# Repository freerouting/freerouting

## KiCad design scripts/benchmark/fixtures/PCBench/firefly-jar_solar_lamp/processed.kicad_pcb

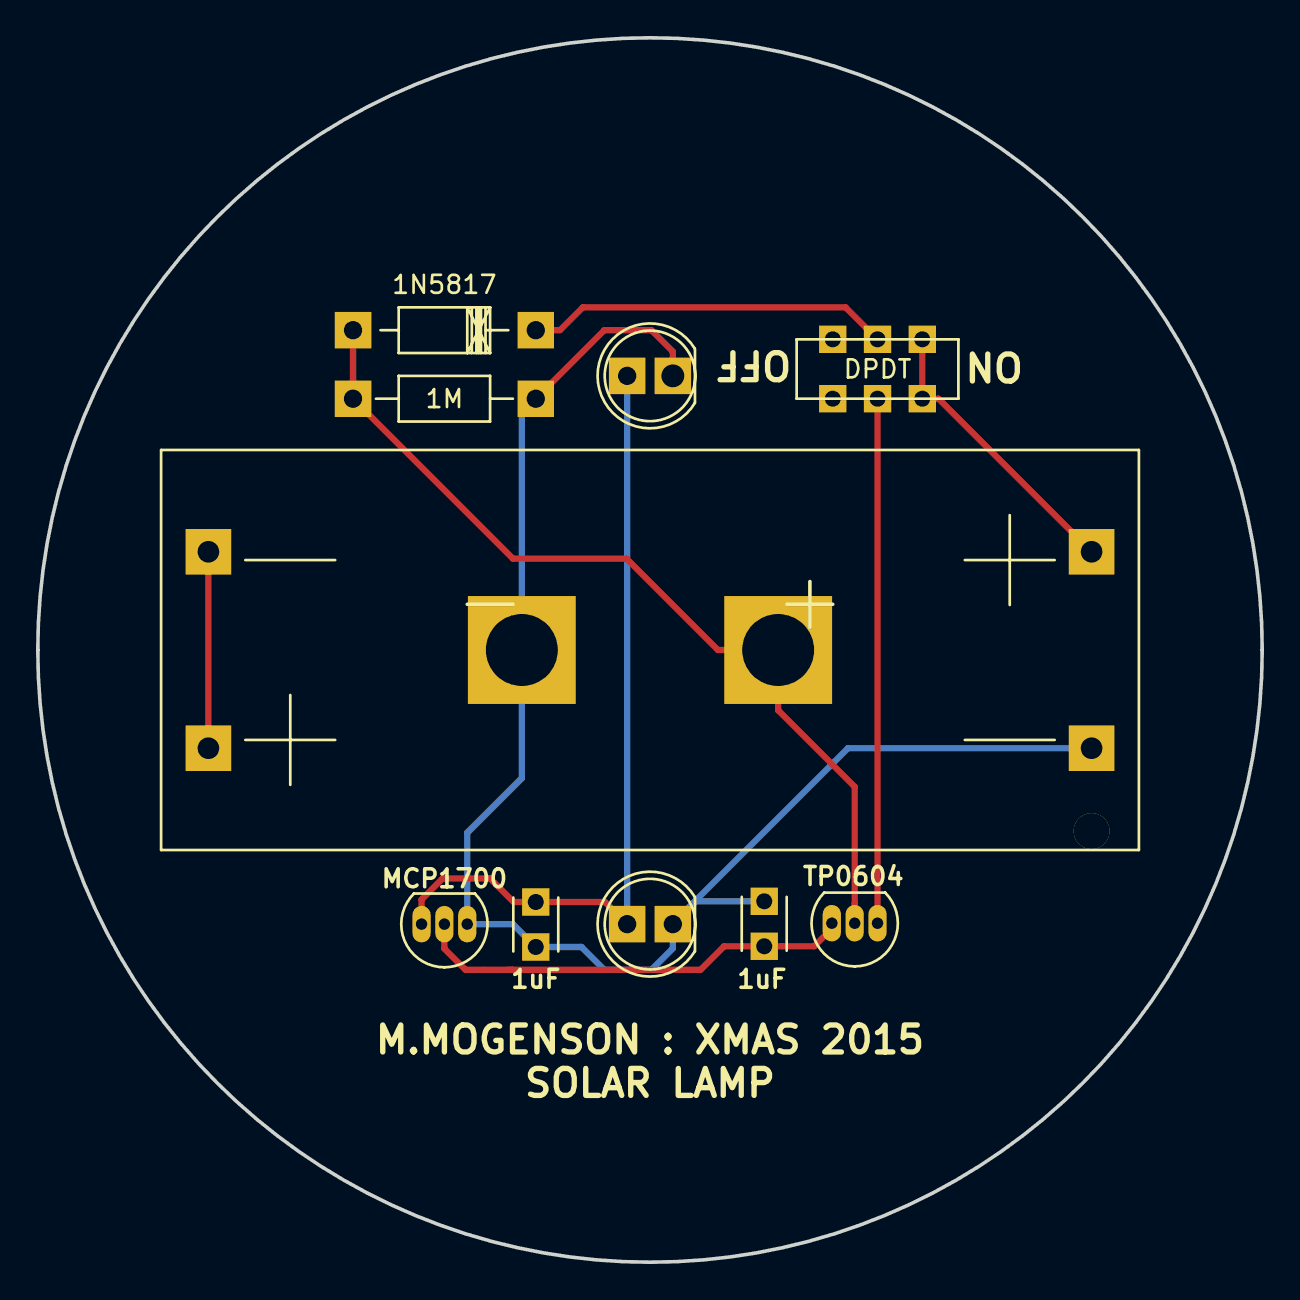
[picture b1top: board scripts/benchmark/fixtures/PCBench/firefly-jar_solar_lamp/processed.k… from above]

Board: 2 copper layers, 68.1 x 68.1 mm, 11 parts (1 on the bottom side), 8 nets.

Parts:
B1: 2x_AAA_battery; Keystone_1077_2x_AAA_battery_holder
BT1: Solar Cell; Adafruit_round_solar_panel
C1, C2: 1uF; C_Disc_D3_P2.5
D1: 1N5817; Diode_DO-41_SOD81_Horizontal_RM10
D2, D3: LED; LED-5MM
Q1: TP0604; TO-92_Inline_Narrow_Oval
R1: 1M; Resistor_Horizontal_RM10mm
SW1: DPDT; DPDT_JS202011CQN_switch
U1: MCP1700; TO-92_Inline_Narrow_Oval

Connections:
GND: B1.2, BT1.2, C1.2, C2.2, D2.1, D3.1, R1.2, U1.1
unnamed: B1.1, B1.4
unnamed: B1.3, SW1.1, SW1.4
unnamed: BT1.1, D1.2, Q1.2, R1.1
unnamed: C1.1, Q1.3, U1.2
unnamed: C2.1, D2.2, D3.2, U1.3
unnamed: D1.1, SW1.2
unnamed: Q1.1, SW1.5

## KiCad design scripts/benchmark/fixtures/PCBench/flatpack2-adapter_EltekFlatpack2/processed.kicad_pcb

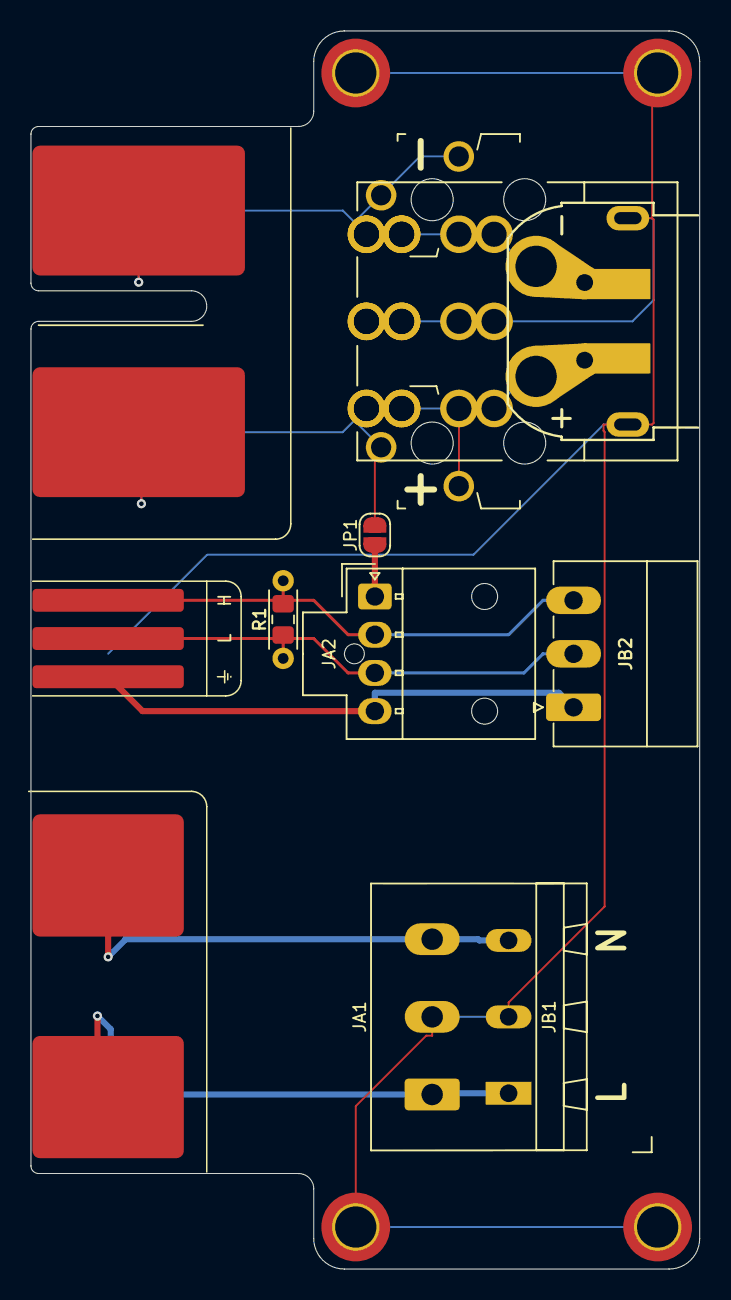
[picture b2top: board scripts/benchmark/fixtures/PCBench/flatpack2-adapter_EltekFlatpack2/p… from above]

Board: 2 copper layers, 43.8 x 81.0 mm, 17 parts (0 on the bottom side), 9 nets.

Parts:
H1, H2, H3, H4: M3; MountingHole_2.7mm_M2.5_ISO7380_Pad_TopBottom
JA1: AC_IN; 1605540000
JA2: CTRL; Molex_Nano-Fit_105309-xx04_1x04_P2.50mm_Combi_3D-V
JA3: DC OUT; TE_2204529-1
JB1: AC_IN; TerminalBlock_WAGO_236-103_1x03_P5.00mm_PadsOnly
JB2: CANBUS; PhoenixContact_MC_1,5_3-G-3.5_1x03_P3.50mm_Horizontal
JB3: DC OUT; TE_2204535-1
JC3: DC OUT; Amass_XT60PW-M_Kombifootprint
JP1: CTRL_VBUS+; SolderJumper-2_P1.3mm_Open_RoundedPad1.0x1.5mm
PC1: Flatpack2; CON_Edge_Flatpack2_AllContacts
R1: 120R; R_0805_2012Metric_Pad1.15x1.40mm_HandSolder
R2: 120R; R_Axial_DIN0204_L3.6mm_D1.6mm_P5.08mm_Horizontal
T1, T2: Keystone 4912; Connector_Keystone_4912_Overlaid

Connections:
/CAN+: JA2.2, JB2.3, PC1.CAN-H, R1.2, R2.2
/CAN-: JA2.3, JB2.2, PC1.CAN-L, R1.1, R2.1
/VBUS+: JA3.1, JB3.1, JB3.4, JC3.2, JP1.1, PC1.DC-POS, T1.1
/VBUS-: JA3.3, JB3.3, JB3.6, JC3.1, PC1.DC-NEG, T2.1
/VCCD: JA2.1, JP1.2
Earth: H1.1, H2.1, H3.1, H4.1, JA1.2, JA3.2, JB1.2, JB3.2, JB3.5, JC3.MP, PC1.AC-E
GNDD: JA2.4, JB2.1, PC1.GNDD
LINE: JA1.1, JB1.1, PC1.AC-L
NEUT: JA1.3, JB1.3, PC1.AC-N

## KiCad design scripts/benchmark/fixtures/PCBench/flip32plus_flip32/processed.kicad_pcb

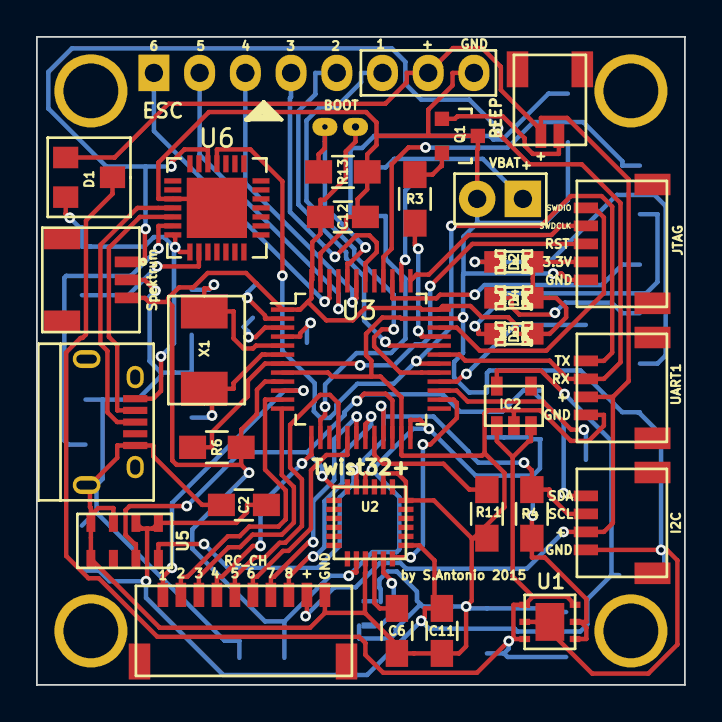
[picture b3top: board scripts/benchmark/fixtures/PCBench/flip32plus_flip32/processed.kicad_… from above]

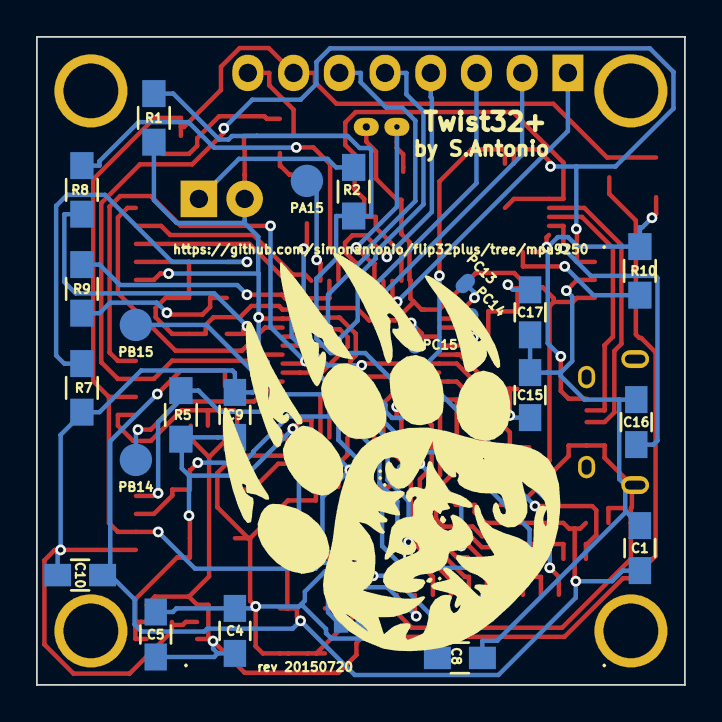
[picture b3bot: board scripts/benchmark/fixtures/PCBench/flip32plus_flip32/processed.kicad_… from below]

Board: 2 copper layers, 36.0 x 36.0 mm, 59 parts (24 on the bottom side), 54 nets.

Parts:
BEEP: BEEPER; Pin_Header_Straight_1x02
BOOT: BOOT; Pin_Header_Straight_1x02
C1, C2, C4, C5, C6, C9, C12, C16: 0.1uF; C_0805_HandSoldering
C8: 10uF; C_0805_HandSoldering
C10, C11, C15, C17: C; C_0805_HandSoldering
CON1: USB; USB_Micro-B
D1: BAV23C; GS3
D2: B; LED-0805
D3: R; LED-0805
D4: G; LED-0805
ESC: ESC OUT; Pin_Header_Straight_1x08
FSYNC-MPU: MPU-JMP; NetTie-I_Connected
I2C: I2C; Pin_Header_Straight_1x04
IC2: MIC5205; SOT-23-5
JP1: MPU-JMP; NetTie-I_Connected
JTAG: JTAG; Pin_Header_Straight_1x05
MNT1, MNT2, MNT3, MNT4: 1pin
PA15: TP; 1pin
PB14, PB15: TP; 1pin
PC13, PC14, PC15: UU5; 1pin
Q1: MMBT29; SOT-23
R1: 11K; R_0805_HandSoldering
R2, R4, R5: 1K; R_0805_HandSoldering
R3: 100; R_0805_HandSoldering
R6, R10: 10k; R_0805_HandSoldering
R7, R8, R9: R; R_0805_HandSoldering
R11, R13: 1k; R_0805_HandSoldering
RC_CH: RECV CHANNELS; Pin_Header_Straight_1x10
Spektrum: Spektrum Satellite Receiver; Pin_Header_Straight_1x03
U1: LP38691; sc70-5
U2: MPU-9250; QFN-24-1EP_3x3mm_Pitch0.4mm
U3: STM32F103CB; LQFP-48_7x7mm_Pitch0.5mm
U5: MS5611-01BA; SOIC-8_3.9x4.9mm_Pitch1.27mm
U6: CP2102; QFN-28-1EP_5x5mm_Pitch0.5mm
UART1: UART 1; Pin_Header_Straight_1x04
VBAT: VBAT; Socket_Strip_Straight_1x02
X1: 8MHZ; Q_49U3HMS

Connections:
/BOOT0: BOOT.1, R13.1, U3.44
/BOOT1: R11.1, U3.20
/LED0: R8.2, U3.40
/LED1: R9.2, U3.39
/MPU_INT: U2.12, U3.26
/NRST: JTAG.3, R6.2, U3.7
/OSC_IN: C17.1, U3.5, X1.2
/OSC_OUT: C15.1, U3.6, X1.1
/POWER_ADC: R1.2, R2.1, U3.14
/PWM1: ESC.6, U3.29
/PWM2: ESC.5, U3.32
/PWM3: ESC.4, U3.42
/PWM4: ESC.3, U3.43
/PWM5: ESC.2, U3.45
/PWM6: ESC.1, U3.46
/RC_CH1: RC_CH.1, U3.10
/RC_CH2: RC_CH.2, U3.11
/RC_CH3: RC_CH.3, U3.12
/RC_CH4: RC_CH.4, U3.13
/RC_CH5: RC_CH.5, U3.16
/RC_CH6: RC_CH.6, U3.17
/RC_CH7: RC_CH.7, U3.18
/RC_CH8: RC_CH.8, U3.19
/RX0: Spektrum.1, U3.31, U6.26, UART1.2
/SCL: I2C.2, R4.2, U2.23, U3.21, U5.8
/SDA: I2C.1, R5.2, U2.24, U3.22, U5.7
/SWDCLK: JTAG.2, U3.37
/SWDIO: JTAG.1, U3.34
/TO_REGS: C4.1, C5.1, D1.3, IC2.1, IC2.3, U1.1, U1.3, U1.6
/TX0: U3.30, U6.25, UART1.1
/UU1: R3.1, U3.33
/UU2: PA15.1, U3.38
/UU3: PC13.1, U3.2
/UU4: PC14.1, U3.3
/UU5: PC15.1, U3.4
/UU7: PB14.1, U3.27
/UU8: PB15.1, U3.28
/VBUS: CON1.1, D1.2, R10.1, U6.7, U6.8
/VCC_IN: BEEP.1, D1.1, ESC.7, I2C.3, RC_CH.9, UART1.3
/VCC_SEN: C1.1, C2.1, C10.1, C11.1, IC2.5, U2.13, U5.1, U5.2
GND: C1.2, C2.2, C4.2, C5.2, C6.2, C8.2, C9.2, C10.2, C11.2, C12.2, C15.2, C16.2, C17.2, CON1.5, CON1.6, ESC.8, FSYNC-MPU.2, I2C.4, IC2.2, JP1.2, JTAG.5, Q1.3, R1.1, R7.2, R11.2, R13.2, RC_CH.10, Spektrum.2, U1.2, U1.7, U2.9, U2.18, U2.20, U3.8, U3.23, U3.35, U3.47, U5.3, U5.4, U5.5, U6.3, U6.29, UART1.4, VBAT.2
unnamed: R10.2, U6.9
unnamed: CON1.2, U6.5
unnamed: CON1.3, U6.4
unnamed: C6.1, U2.10
unnamed: FSYNC-MPU.1, U2.11
unnamed: C16.1, U6.6
unnamed: D3.2, R8.1
unnamed: D4.2, R9.1
unnamed: D2.2, R7.1
unnamed: Q1.2, R3.2
unnamed: BEEP.2, Q1.1
unnamed: R2.2, VBAT.1
VCC: BOOT.2, C8.1, C9.1, C12.1, D2.1, D3.1, D4.1, JTAG.4, R4.1, R5.1, R6.1, Spektrum.3, U1.4, U1.5, U2.8, U2.22, U3.1, U3.9, U3.24, U3.36, U3.48
